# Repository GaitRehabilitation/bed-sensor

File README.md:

# Bed Sensor

## Background

This sensor is built around the open source schematic of the Ardunio Pro Mini and the seperate parts we're tested sepertly and the final board was printed from [oshPark](https://oshpark.com/). This is an experemential sensor that makes sure patients roll over within a fixed interval. The model uses a state machine with two states: COUNTING_STATE, and a ROTATING_STATE. The counting state samples the direction of the acceleration vector and during the ROTATING_STATE, the arc angle between the current vector and the sampled data from the counting state determins the rotation of the device from the resting state. A average filter is sampled from the current resting angle of the sensor is sampled by taking 20% of the current sample vector and 80% of the current resting angle. This is a mitigation strategy that avoids sampling from sudden movments and affecting the angle of the sensor. The counting state is reset if the devaition from the scalar vector is greater then .35 g's.  

## Programming

Tools:
- [SCONS](https://scons.org/)
- [avrdud](https://www.nongnu.org/avrdude/)
- [avr-gcc](https://gcc.gnu.org/wiki/avr-gcc)
- [minicore](https://github.com/MCUdude/MiniCore)

building cpp code `scons build`. The compiled code produces a hex 

```avrdude -c <programmer> -p atmega328 -b 57600  -U flash:w:main.hex -U lfuse:w:0xff:m -U hfuse:w:0xd1:m -U efuse:w:0xff:m```

[Fuse Calculator](http://eleccelerator.com/fusecalc/fusecalc.php?chip=atmega328p)

## Maintainers

The current maintainers of this repository are:

* Michael Pollind <polli104@mail.chapman.edu>

# License

```
/**
* Copyright 2018 GaitRehabilitation
*
* Licensed under the Apache License, Version 2.0 (the "License");
* you may not use this file except in compliance with the License.
* You may obtain a copy of the License at
*
*     http://www.apache.org/licenses/LICENSE-2.0
*
* Unless required by applicable law or agreed to in writing, software
* distributed under the License is distributed on an "AS IS" BASIS,
* WITHOUT WARRANTIES OR CONDITIONS OF ANY KIND, either express or implied.
* See the License for the specific language governing permissions and
* limitations under the License.
*/

```

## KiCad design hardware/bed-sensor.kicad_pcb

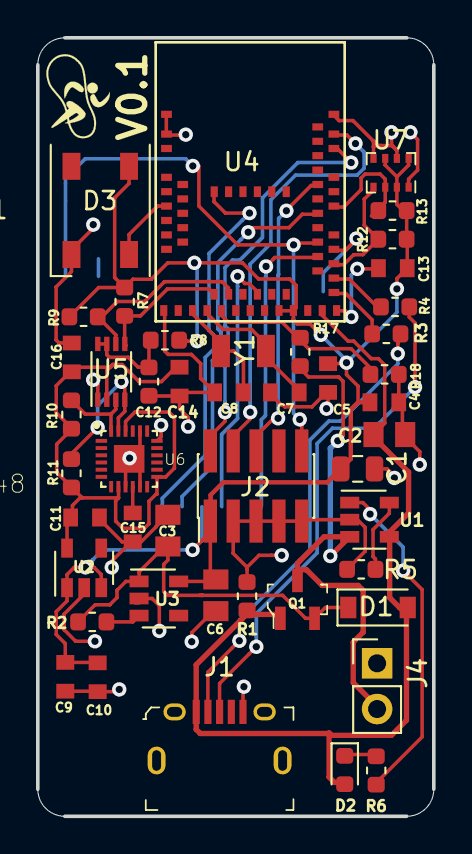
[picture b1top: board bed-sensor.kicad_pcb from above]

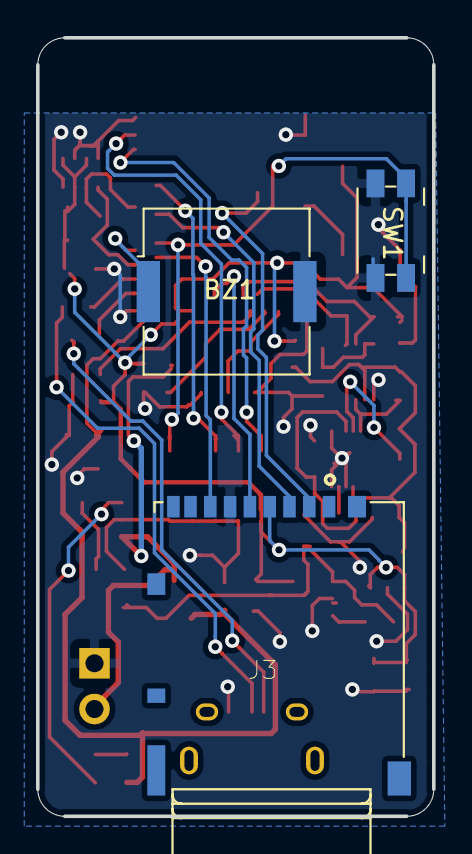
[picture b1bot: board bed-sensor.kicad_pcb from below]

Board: 2 copper layers, 22.0 x 43.2 mm, 49 parts (3 on the bottom side), 35 nets.

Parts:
BZ1: Buzzer; Buzzer_Murata_PKMCS0909E4000-R1
C1, C2, C3, C6: 10uF; C_0805_2012Metric
C4, C5, C9, C13, C14, C15, C16: .1uF; C_0603_1608Metric
C7, C8: 12pF; C_0603_1608Metric
C10, C11: 1uF; C_0603_1608Metric
C12: 100PF; C_0603_1608Metric
D1: D_Schottky; D_SOD-123
D2: LED; D_0603_1608Metric
D3: WS2812B; LED_WS2812B_PLCC4_5.0x5.0mm_P3.2mm
J1: USB_B_Mini; USB_Micro_B_Female_10118194-0001LF
J2: Conn_ARM_JTAG_SWD_10; PinHeader_2x05_P1.27mm_Vertical_SMD
J3: DM3AT-SF-PEJM5; HRS_DM3AT-SF-PEJM5
J4: Conn_01x02; PinHeader_1x02_P2.54mm_Vertical
Q1: Q_PMOS_GSD; SOT-23-3
R1, R2, R17, R18: 100K; R_0603_1608Metric
R3, R4: 22; R_0603_1608Metric
R5, R7, R9, R10, R11, R12, R13: 4.7K; R_0603_1608Metric
R6: 1K; R_0603_1608Metric
R8: 200k; R_0603_1608Metric
SW1: SW_Push; Panasonic_EVQPUJ_EVQPUA
U1: MCP73831-2-OT; SOT-23-5
U2: TLV70218_SOT23-5; SOT-23-5
U3: AP2112K-3.3; SOT-23-5
U4: MDBT50Q-1M
U5: PCA9306; VSSOP-8_2.3x2mm_P0.5mm
U6: ICM-20948
U7: BMP280; Bosch_LGA-8_2x2.5mm_P0.65mm_ClockwisePinNumbering
Y1: 32.768; FC-135 32.7680KA-AC3

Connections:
+1V8: C11.1, C14.2, C16.2, R10.2, R11.2, U2.5, U5.2, U6.8, U6.13, U6.22
+3V3: C1.1, C4.1, C5.1, C6.1, C9.1, C10.1, C13.2, D3.1, J2.1, J3.4, R7.2, R8.2, R9.2, R12.2, R13.2, U2.1, U2.3, U3.5, U4.28, U4.30, U7.2, U7.6, U7.8
+BATT: J4.2, Q1.3, R17.1, U1.3
BMP_SCL: R12.1, U4.37, U7.4
BMP_SDA: R13.1, U4.44, U7.3
BUZZER: BZ1.1, U4.39
GND: BZ1.2, C1.2, C2.2, C3.2, C4.2, C5.2, C6.2, C7.2, C8.2, C9.2, C10.2, C11.2, C12.2, C13.1, C14.1, C15.1, C16.1, D3.3, J1.5, J2.3, J2.5, J2.7, J2.9, J3.6, J4.1, R1.2, R5.2, R18.2, SW1.2, U1.2, U2.2, U3.2, U4.1, U4.2, U4.15, U4.33, U4.55, U5.1, U6.9, U6.11, U6.18, U6.20, U6.25, U7.1, U7.5, U7.7
NEO_LED: D3.4, U4.8
unnamed: C3.1, D1.1, Q1.2, R2.2, U3.1
unnamed: C7.1, U4.18, Y1.1
unnamed: C8.1, U4.17, Y1.2
unnamed: C12.1, R8.1, U5.7, U5.8
unnamed: C15.2, U6.10
unnamed: D2.1, R6.2
unnamed: R2.1, U3.3
unnamed: R3.2, U4.34
unnamed: R4.2, U4.35
unnamed: R5.1, U1.5
unnamed: R6.1, U1.1
unnamed: R10.1, U5.3, U6.24
unnamed: R11.1, U5.4, U6.23
RESET: J2.10, SW1.1, U4.40
SCL_MPU: R7.1, U4.19, U5.5
SDA_MPU: R9.1, U4.21, U5.6
SD_CS: J3.2, U4.56
SD_MISO: J3.7, U4.38
SD_MOSI: J3.3, U4.43
SD_SCK: J3.5, U4.25
SWCLK: J2.4, U4.53
SWDIO: J2.2, U4.51
SWO: J2.6, U4.47
USB_D+: J1.3, R4.1
USB_D-: J1.2, R3.1
VBUS: C2.1, D1.2, D2.2, J1.1, Q1.1, R1.1, U1.4, U4.32
VDIV: R17.2, R18.1, U4.20

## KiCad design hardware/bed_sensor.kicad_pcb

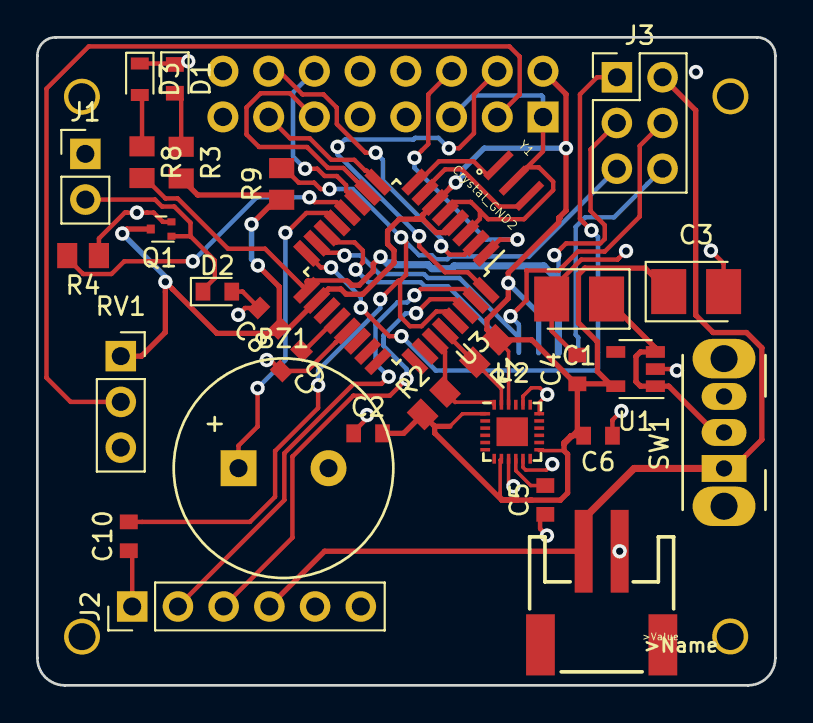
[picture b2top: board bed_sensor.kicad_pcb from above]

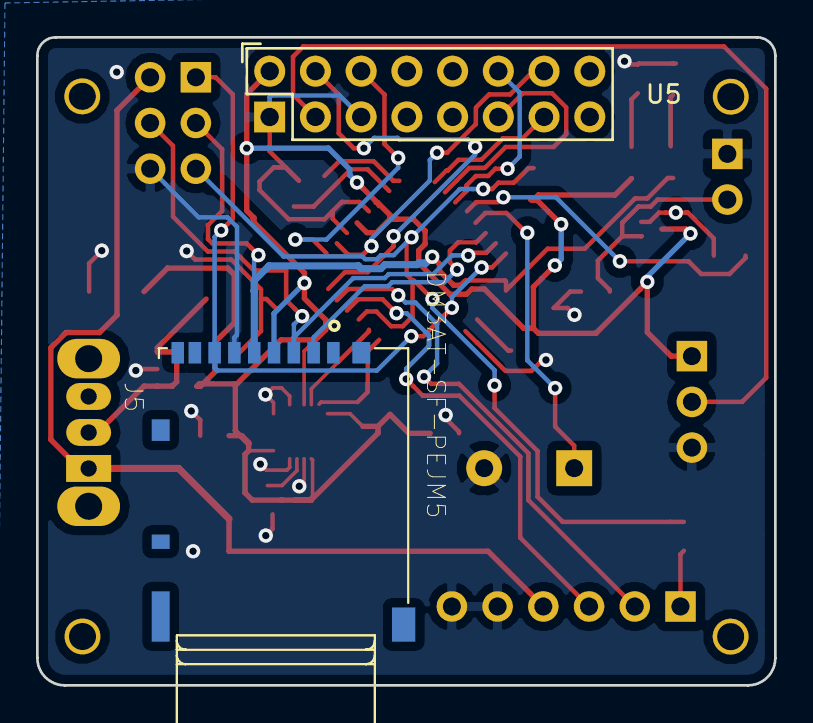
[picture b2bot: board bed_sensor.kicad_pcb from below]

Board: 2 copper layers, 41.0 x 36.0 mm, 32 parts (2 on the bottom side), 31 nets.

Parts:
BZ1: Buzzer; PS1240P02BT
C1: 10uF; CP_Tantalum_Case-T_EIA-3528-12_Reflow
C2: 10nF; C_0603_1608Metric
C3: 10uF; CP_Tantalum_Case-B_EIA-3528-21_Reflow
C4, C5, C6: .1uF; C_0603_1608Metric
C8, C9, C10: .1uf; C_0603_1608Metric
D1: LED; LED_0603_1608Metric
D2: D; D_0603_1608Metric
D3: LD271; LED_0603_1608Metric_Pad0.67x1.00mm_HandSolder
J1: Conn_01x02; PinHeader_1x02_P2.54mm_Vertical
J2: Conn_01x06; PinHeader_1x06_P2.54mm_Vertical
J3: ISP; PinHeader_2x03_P2.54mm_Vertical
J4: Conn_01x02; JSTPH2
J5: DM3AT-SF-PEJM5; HRS_DM3AT-SF-PEJM5
Q1: 2N2219; SOT-723
R1, R2, R3, R9: 10k; R_0805_2012Metric
R4: 1K; R_0805_2012Metric
R8: 330; R_0805_2012Metric
RV1: 10K; PinSocket_1x03_P2.54mm_Vertical
SW1: SW_SPST; SW_CuK_OS102011MA1QN1_SPDT_Angled
U1: MIC5205-3.3; SOT-23-5
U2: MPU-9250; QFN-24-1EP_3x3mm_P0.4mm_EP1.75x1.6mm
U3: ATMEGA328-AU; TQFP-32_7x7mm_P0.8mm
U5: CFAH0802D-YYH-JP
Y1: Crystal_GND2; OSC_CSTCE8M00G55-R0

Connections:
+3V3: C2.2, C3.1, C4.1, C6.2, C8.1, J5.4, Q1.3, R1.1, R2.1, R3.2, R9.1, RV1.1, U1.5, U2.1, U2.8, U2.13, U2.22, U3.4, U3.6, U3.18, U5.2
/Ardunio/DTR: C10.1, J2.1
/Ardunio/RESET: C10.2, J3.5, R9.2, U3.29
/Ardunio/RX1: J2.3, U3.30
/Ardunio/TX0: J2.2, U3.31
Buzzer: BZ1.1, U3.13
CS: J5.2, U3.14
DB4: U3.10, U5.11
DB5: U3.11, U5.12
DB6: U3.9, U5.13
DB7: U3.2, U5.14
Display_Enable: U3.1, U5.6
GND: BZ1.2, C1.2, C2.1, C3.2, C4.2, C5.1, C6.1, C8.2, C9.2, D1.1, D2.2, D3.1, J1.1, J2.5, J2.6, J3.6, J4.1, J5.6, RV1.3, U1.2, U2.9, U2.11, U2.18, U2.20, U3.3, U3.5, U3.21, U5.1, U5.5, Y1.2
MISO: J3.1, J5.7, U3.16
MOSI: J3.4, J5.3, U3.15
unnamed: C1.1, SW1.2, U1.1, U1.3
unnamed: C5.2, U2.10
unnamed: C9.1, U3.20
unnamed: D1.2, R3.1
unnamed: D2.1, J1.2, Q1.1
unnamed: D3.2, R8.1
unnamed: Q1.2, R4.1
unnamed: RV1.2, U5.3
unnamed: U3.7, Y1.3
unnamed: U3.8, Y1.1
RS: U3.32, U5.4
SCK: J3.3, J5.5, R8.2, U3.17
SCL_MPU: R1.2, U2.23, U3.28
SDA_MPU: R2.2, U2.24, U3.27
VCC: J2.4, J3.2, J4.2, SW1.1
Vibration: R4.2, U3.12

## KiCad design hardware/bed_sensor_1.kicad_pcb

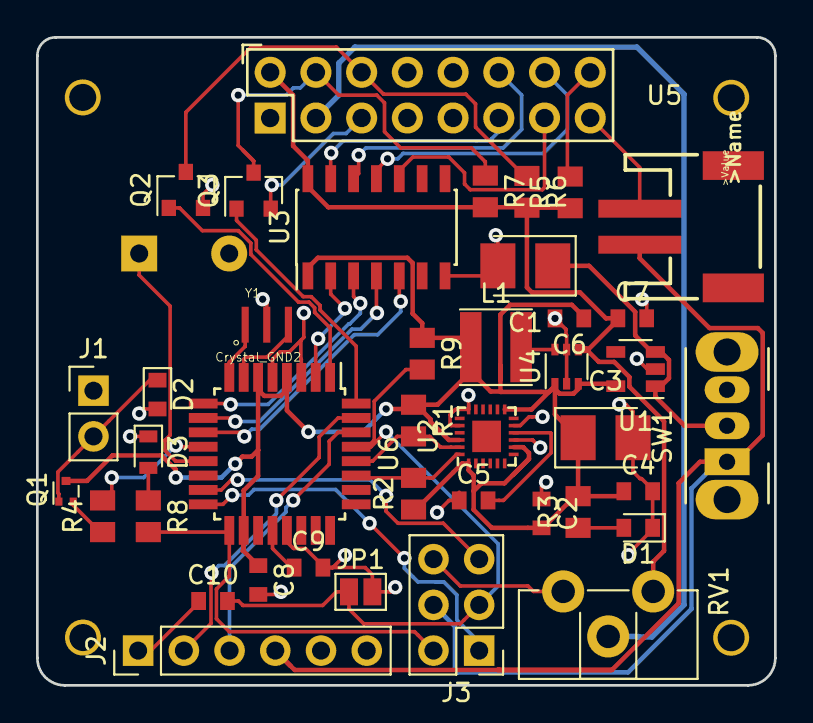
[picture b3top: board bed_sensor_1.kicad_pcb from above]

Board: 2 copper layers, 41.0 x 36.0 mm, 41 parts (1 on the bottom side), 39 nets.

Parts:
BZ1: Buzzer; PS1240P02BT
C1: 10uF; CP_Tantalum_Case-T_EIA-3528-12_Reflow
C2: 10nF; C_0603_1608Metric
C3: 10uF; CP_Tantalum_Case-B_EIA-3528-21_Reflow
C4, C5: .1uF; C_0603_1608Metric
C6: 1uF; C_0603_1608Metric
C7: 10uF; C_0603_1608Metric
C8, C9, C10: .1uf; C_0603_1608Metric
D1: LED; LED_0603_1608Metric
D2: D; D_0603_1608Metric
D3: LD271; LED_0603_1608Metric_Pad0.67x1.00mm_HandSolder
J1: Conn_01x02; PinHeader_1x02_P2.54mm_Vertical
J2: Conn_01x06; PinHeader_1x06_P2.54mm_Vertical
J3: ISP; PinHeader_2x03_P2.54mm_Vertical
J4: Conn_01x02; JSTPH2
JP1: Jumper_NO_Small; SolderJumper-2_P1.3mm_Open_Pad1.0x1.5mm
L1: 10uH; L_Taiyo-Yuden_NR-40xx
Q1: 2N2219; SOT-723
Q2, Q3: BSS138; SOT-23
R1, R2, R3, R6, R7, R9: 10k; R_0805_2012Metric
R4: 1K; R_0805_2012Metric
R5: 220; R_0805_2012Metric
R8: 330; R_0805_2012Metric
RV1: 10K; Potentiometer_Trimmer_ACP_CA9h2.5_Vertical_Px2.5mm_Py5.0mm
SW1: SW_SPST; SW_CuK_OS102011MA1QN1_SPDT_Angled
U1: MIC5205-3.3; SOT-23-5
U2: MPU-9250; QFN-24-1EP_3x3mm_P0.4mm_EP1.75x1.6mm
U3: TXB0104D; SOIC-14_3.9x8.7mm_P1.27mm
U4: LTC3525-5; SOT-363_SC-70-6
U5: CFAH0802D-YYH-JP
U6: ATMEGA328-AU; TQFP-32_7x7mm_Pitch0.8mm
Y1: Crystal_GND2; OSC_CSTCE8M00G55-R0

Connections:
+3V3: C2.2, C3.1, C4.1, C6.1, C8.1, L1.1, Q1.3, R1.1, R2.1, R3.2, R9.1, U1.5, U2.1, U2.8, U2.13, U2.22, U3.1, U4.1, U4.3, U6.4, U6.6, U6.18
+5V: C7.1, R5.1, R6.2, R7.2, RV1.1, U3.14, U4.4, U5.2
/Ardunio/DTR: C10.1, J2.1
/Ardunio/MISO: J3.1, U6.16
/Ardunio/MOSI: J3.5, U6.15
/Ardunio/RESET: C10.2, J3.3, JP1.1, R9.2, U6.29
/Ardunio/RX1: J2.3, U6.30
/Ardunio/SCK: J3.2, R8.2, U6.17
/Ardunio/TX0: J2.2, U6.31
Buzzer: BZ1.1, U6.13
DB4: U3.4, U6.10
DB5: U3.5, U6.11
DB6: U3.3, U6.9
DB7: U3.2, U6.2
Display_Enable: Q2.1, U6.1
GND: BZ1.2, C1.2, C2.1, C3.2, C4.2, C5.1, C6.2, C7.2, C8.2, C9.2, D1.1, D2.2, D3.1, J1.1, J2.5, J2.6, J3.6, J4.1, JP1.2, Q2.2, Q3.2, RV1.3, U1.2, U2.9, U2.11, U2.18, U2.20, U3.7, U4.2, U4.5, U5.1, U5.5, U5.16, U6.3, U6.5, U6.21, Y1.2
unnamed: C1.1, SW1.2, U1.1, U1.3
unnamed: C5.2, U2.10
unnamed: C9.1, U6.20
unnamed: D1.2, R3.1
unnamed: D2.1, J1.2, Q1.1
unnamed: D3.2, R8.1
unnamed: L1.2, U4.6
unnamed: Q1.2, R4.1
unnamed: Q2.3, R6.1, U5.6
unnamed: Q3.3, R7.1, U5.4
unnamed: R5.2, U5.15
unnamed: RV1.2, U5.3
unnamed: U3.10, U5.14
unnamed: U3.11, U5.13
unnamed: U3.12, U5.12
unnamed: U3.13, U5.11
unnamed: U6.7, Y1.3
unnamed: U6.8, Y1.1
RS: Q3.1, U6.32
SCL_MPU: R1.2, U2.23, U6.28
SDA_MPU: R2.2, U2.24, U6.27
VCC: J2.4, J3.4, J4.2, SW1.1
Vibration: R4.2, U6.12

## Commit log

2018-04-05 start
2018-04-05 add csv
2018-04-05 fixed layout
2018-04-05 updated csv
2018-04-06 twekaed paths
2018-04-06 tweak
2018-04-06 added measurements
2018-06-01 added CFAH0802d
2018-06-02 updated schematic
2018-06-02 updated design
2018-06-12 updated pcb layout
2018-06-13 corrected pinout for NHD display
2018-06-19 added SD card
2018-06-22 updated board
2018-06-22 added toggle button to side of board
2018-08-30 updated design to accomidate screen better
2018-08-30 working out missing sd card`
2018-08-30 flipped screen
2018-08-30 cleaned up board
2018-08-30 tweaked layout
2018-08-30 fixed silk and mask for screen
2018-08-30 shifted components arround to accomidate buzzer
2018-09-19 updated layout
2018-09-24 updated layout for thumb pot
2018-11-19 modified design slightly and fixed problems with layout
2018-11-19 updated schematic removed old kicad design
2018-11-19 added readme
2018-11-20 reimplementing with state model
2018-11-20 tweaked firmware for angle
2018-11-20 added sdfat and added update rate for display
2018-11-20 add sdfat
2018-11-21 tweaked model and also seralized to binary
2018-11-21 added missing time
2018-11-21 fixed new bin for logging
2018-11-21 tweaked code
2018-11-21 increased time
2018-11-21 added resting time clock
2019-01-18 fixed buzzer issue
2019-01-18 tweaked movement trigger
2019-01-20 tweaked setup
2019-01-20 moved string to data
2019-01-21 added watchdog timer
2019-01-21 tweaked watchdog
2019-01-30 updated code
2019-01-30 adding moving avg
2019-01-31 fixed lcd init
2019-02-07 tweaked sd
2019-02-08 remove timer for updating movement
2019-03-01 added 1000 deg/s
2019-03-21 added MDBT50Q-1M
2019-03-22 implemented firmware and hardware
2019-03-22 added ICM library
2019-03-30 added symbolds and started to lay out board
2019-03-30 started building board
2019-03-30 moved pin
2019-03-30 updated and added csv
2019-03-31 tweaked board
2019-04-01 moved over to zephyr
2019-04-01 added vagrent
2019-04-02 removed docker
2019-04-03 updated kicad and vagrant file
2019-04-04 updated footprints
2019-04-04 finalized order list
2019-04-04 update layout
2019-04-04 added bom file
2019-04-04 rounded off corners
2019-04-05 tweaked csv
2019-04-05 corrected csv
2019-04-05 tweaked
2019-04-05 removed extra
2019-04-05 removed west
2019-04-07 added drivers and board
2019-04-08 updated dts file and deleted drivers
2019-05-18 started working on implementing ws2812
2019-05-18 added main
2019-05-20 updated dts
2019-05-28 added buzzer
2019-05-28 fixed build
2019-05-29 updated dts for pressure sensor
2019-06-06 added device and updated configs
2019-11-22 added readme with images
